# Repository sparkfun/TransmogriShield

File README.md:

SparkFun TransmogriShield
========================================

[*SparkFun TransmogriShield (DEV-11469)*](https://www.sparkfun.com/products/11469)

The Arduino Leonardo arrived on the scene to great applause. This was followed by the creeping realization that, because of the new microcontroller, all of our favorite SPI or I2C-based Arduino shields would be incompatible.
By using an arrangement of surface-mount headers to “intercept” the incoming pins and shift them around, the TransmogriShield takes the SPI and I2C lines from their new, less convenient, homes at the ICSP header and D2/3 pins, and moves them back into classic Arduino position: SPI on D11-13 and I2C on A4/A5. 

 Repository Contents
-------------------

* **/Hardware** - Eagle design files (.brd, .sch)
* **/Production** - Production panel files (.brd)

Documentation
--------------
* **[SparkFun Fritzing repo](https://github.com/sparkfun/Fritzing_Parts)** - Fritzing diagrams for SparkFun products.
* **[SparkFun 3D Model repo](https://github.com/sparkfun/3D_Models)** - 3D models of SparkFun products. 

License Information
-------------------
This product is _**open source**_! 

The **hardware** is released under [Creative Commons ShareAlike 4.0 International](https://creativecommons.org/licenses/by-sa/4.0/).

Please use, reuse, and modify these files as you see fit. Please maintain attribution to SparkFun Electronics and release anything derivative under the same license.

Distributed as-is; no warranty is given.

- Your friends at SparkFun.

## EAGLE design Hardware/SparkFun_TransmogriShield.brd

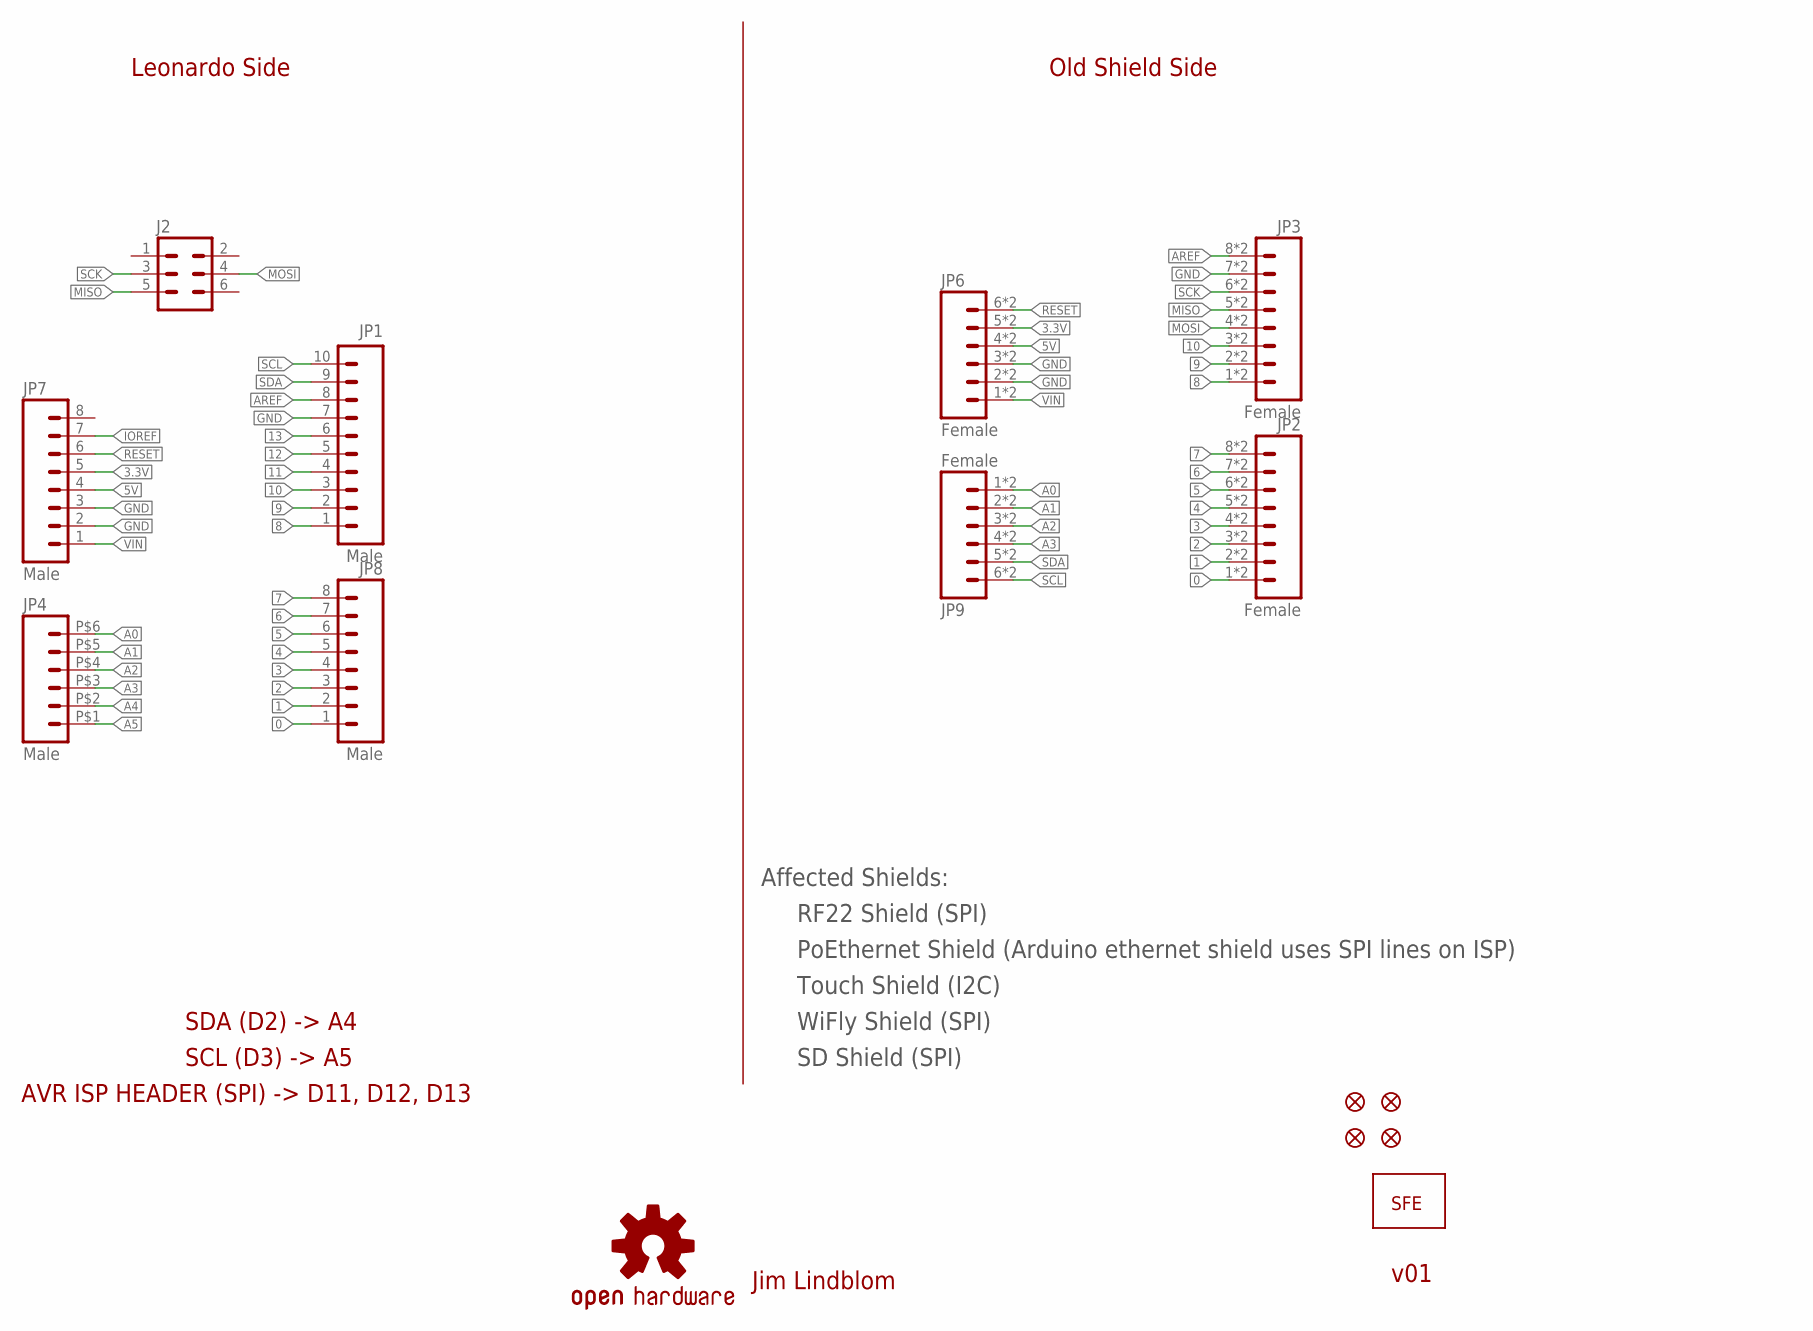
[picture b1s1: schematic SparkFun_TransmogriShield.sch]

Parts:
J2: Female; 2X3_SMD
JP1: Male; 1X10_SMD_MALE
JP2, JP3: Female; 1X08_SMD_COMBINED
JP4: Male; 1X06_SMD_MALE
JP6, JP9: Female; 1X06_SMD_STRAIGHT_COMBO
JP7, JP8: Male; 1X08_SMD_MALE
JP10: LOGO-SFESK; SFE-LOGO-FLAME
JP11, JP12, JP13, JP14: FIDUCIALUFIDUCIAL; MICRO-FIDUCIAL
U$1: OSHW-LOGOS; OSHW-LOGO-S

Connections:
0: JP2.1, JP2.1@2 (1), JP8.1
1: JP2.2, JP2.2@2 (2), JP8.2
2: JP2.3, JP2.3@2 (3), JP8.3
3: JP2.4, JP2.4@2 (4), JP8.4
3.3V: JP6.5, JP6.5-2 (5), JP7.5
4: JP2.5, JP2.5@2 (5), JP8.5
5: JP2.6, JP2.6@2 (6), JP8.6
5V: JP6.4, JP6.4-2 (4), JP7.4
6: JP2.7, JP2.7@2 (7), JP8.7
7: JP2.8, JP2.8@2 (8), JP8.8
8: JP1.1, JP3.1, JP3.1@2 (1)
9: JP1.2, JP3.2, JP3.2@2 (2)
10: JP1.3, JP3.3, JP3.3@2 (3)
11: JP1.4
12: JP1.5
13: JP1.6
A0: JP4.P$6 (6), JP9.1, JP9.1-2 (1)
A1: JP4.P$5 (5), JP9.2, JP9.2-2 (2)
A2: JP4.P$4 (4), JP9.3, JP9.3-2 (3)
A3: JP4.P$3 (3), JP9.4, JP9.4-2 (4)
A4: JP4.P$2 (2)
A5: JP4.P$1 (1)
AREF: JP1.8, JP3.8, JP3.8@2 (8)
GND: JP1.7, JP3.7, JP3.7@2 (7), JP6.2, JP6.2-2 (2), JP6.3, JP6.3-2 (3), JP7.2, JP7.3
IOREF: JP7.7
MISO: J2.5, JP3.5, JP3.5@2 (5)
MOSI: J2.4, JP3.4, JP3.4@2 (4)
RESET: JP6.6, JP6.6-2 (6), JP7.6
SCK: J2.3, JP3.6, JP3.6@2 (6)
SCL: JP1.10, JP9.6, JP9.6-2 (6)
SDA: JP1.9, JP9.5, JP9.5-2 (5)
VIN: JP6.1, JP6.1-2 (1), JP7.1

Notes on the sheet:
Affected Shields:
RF22 Shield (SPI)
PoEthernet Shield (Arduino ethernet shield uses SPI lines on ISP)
Touch Shield (I2C)
WiFly Shield (SPI)
SD Shield (SPI)
Jim Lindblom
Leonardo Side
Old Shield Side
SDA (D2) -> A4
SCL (D3) -> A5
AVR ISP HEADER (SPI) -> D11, D12, D13
v01

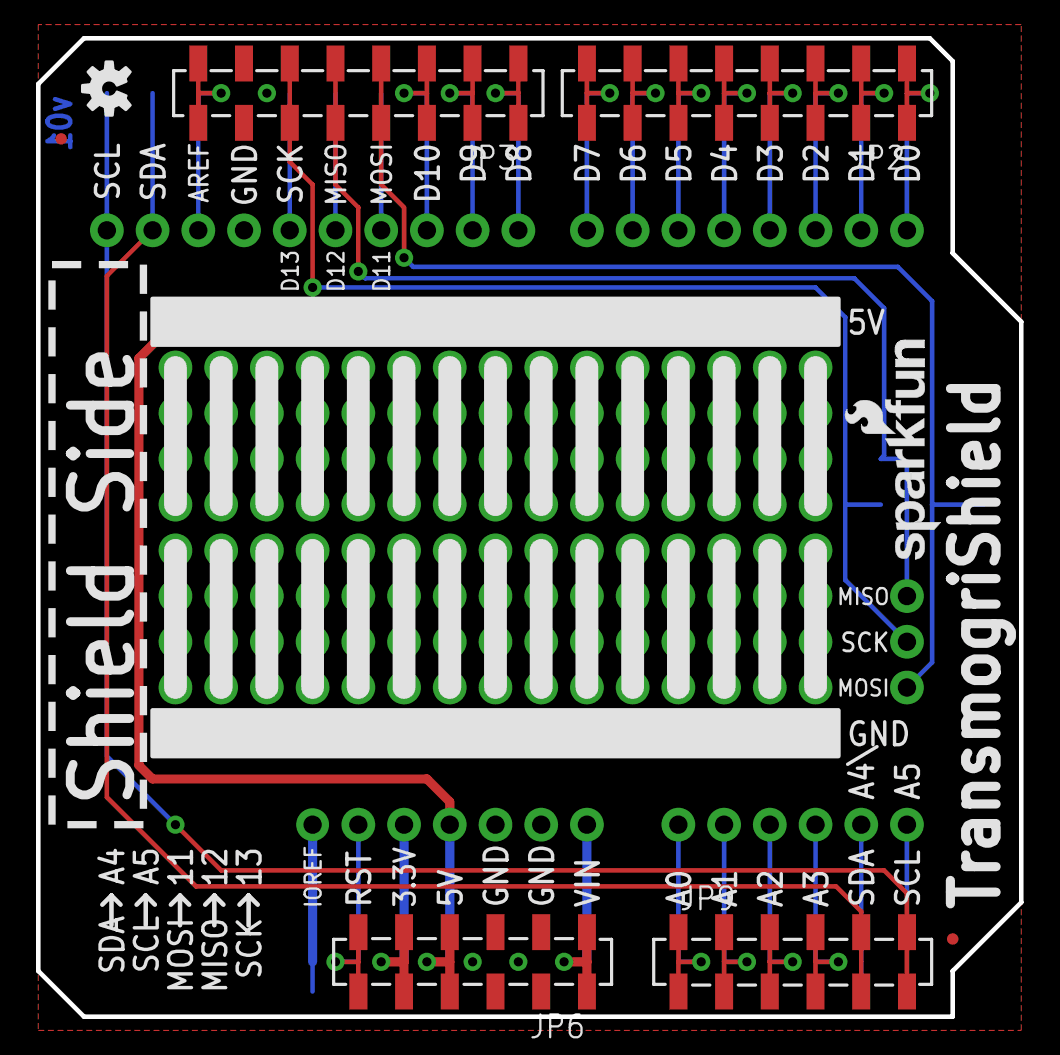
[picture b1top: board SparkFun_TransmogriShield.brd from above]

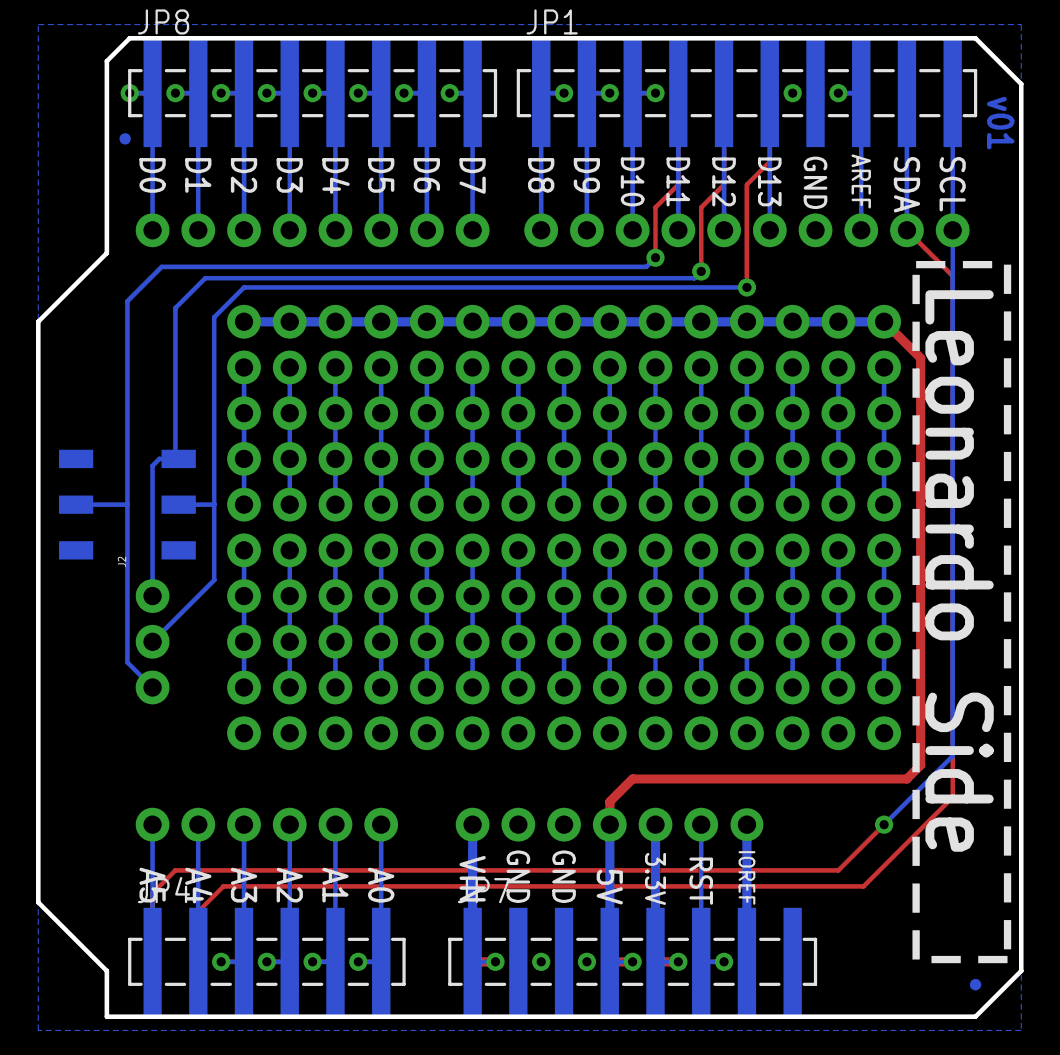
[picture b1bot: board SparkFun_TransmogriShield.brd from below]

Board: 2 copper layers, 54.6 x 54.4 mm, 16 parts (7 on the bottom side), 26 nets.

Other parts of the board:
JP5: LOGO-SFENW2; SFE-NEW-WEB

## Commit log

2015-05-12 Adding hardware files

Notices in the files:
parts and their libraries:
SparkFun-Aesthetics: Licensing: CC v3.0 Share-Alike You are welcome to use this library for commercial purposes.
SparkFun-Aesthetics: Released under the Creative Commons
SparkFun-Aesthetics: http://creativecommons.org/licenses/by-sa/3.0
